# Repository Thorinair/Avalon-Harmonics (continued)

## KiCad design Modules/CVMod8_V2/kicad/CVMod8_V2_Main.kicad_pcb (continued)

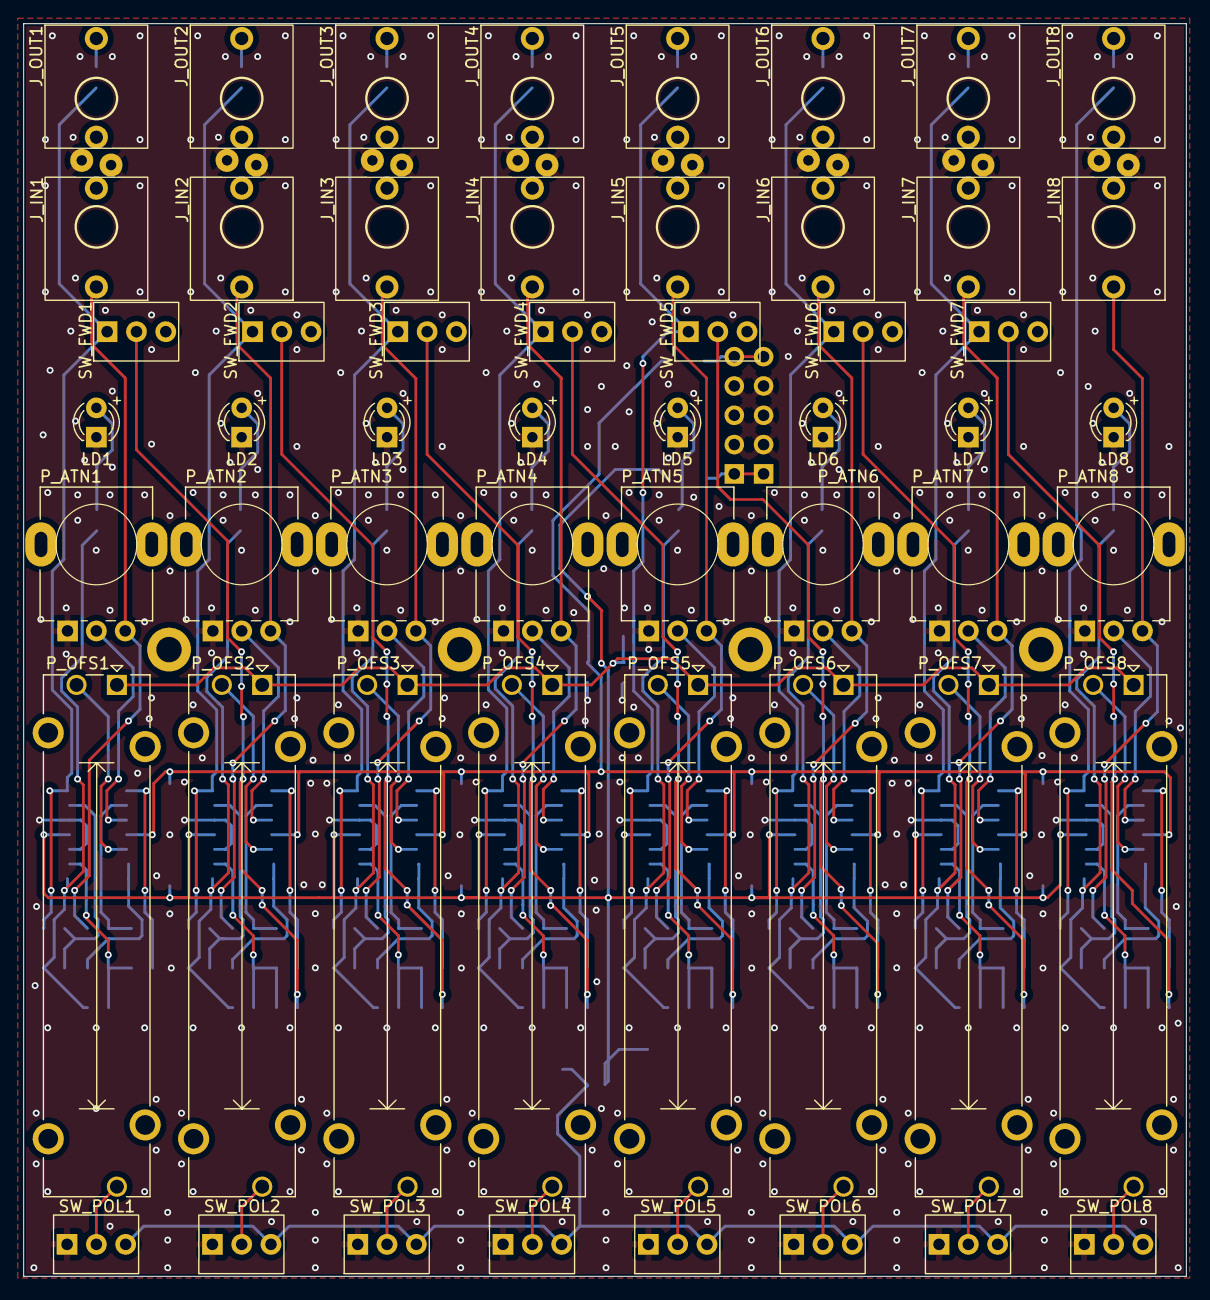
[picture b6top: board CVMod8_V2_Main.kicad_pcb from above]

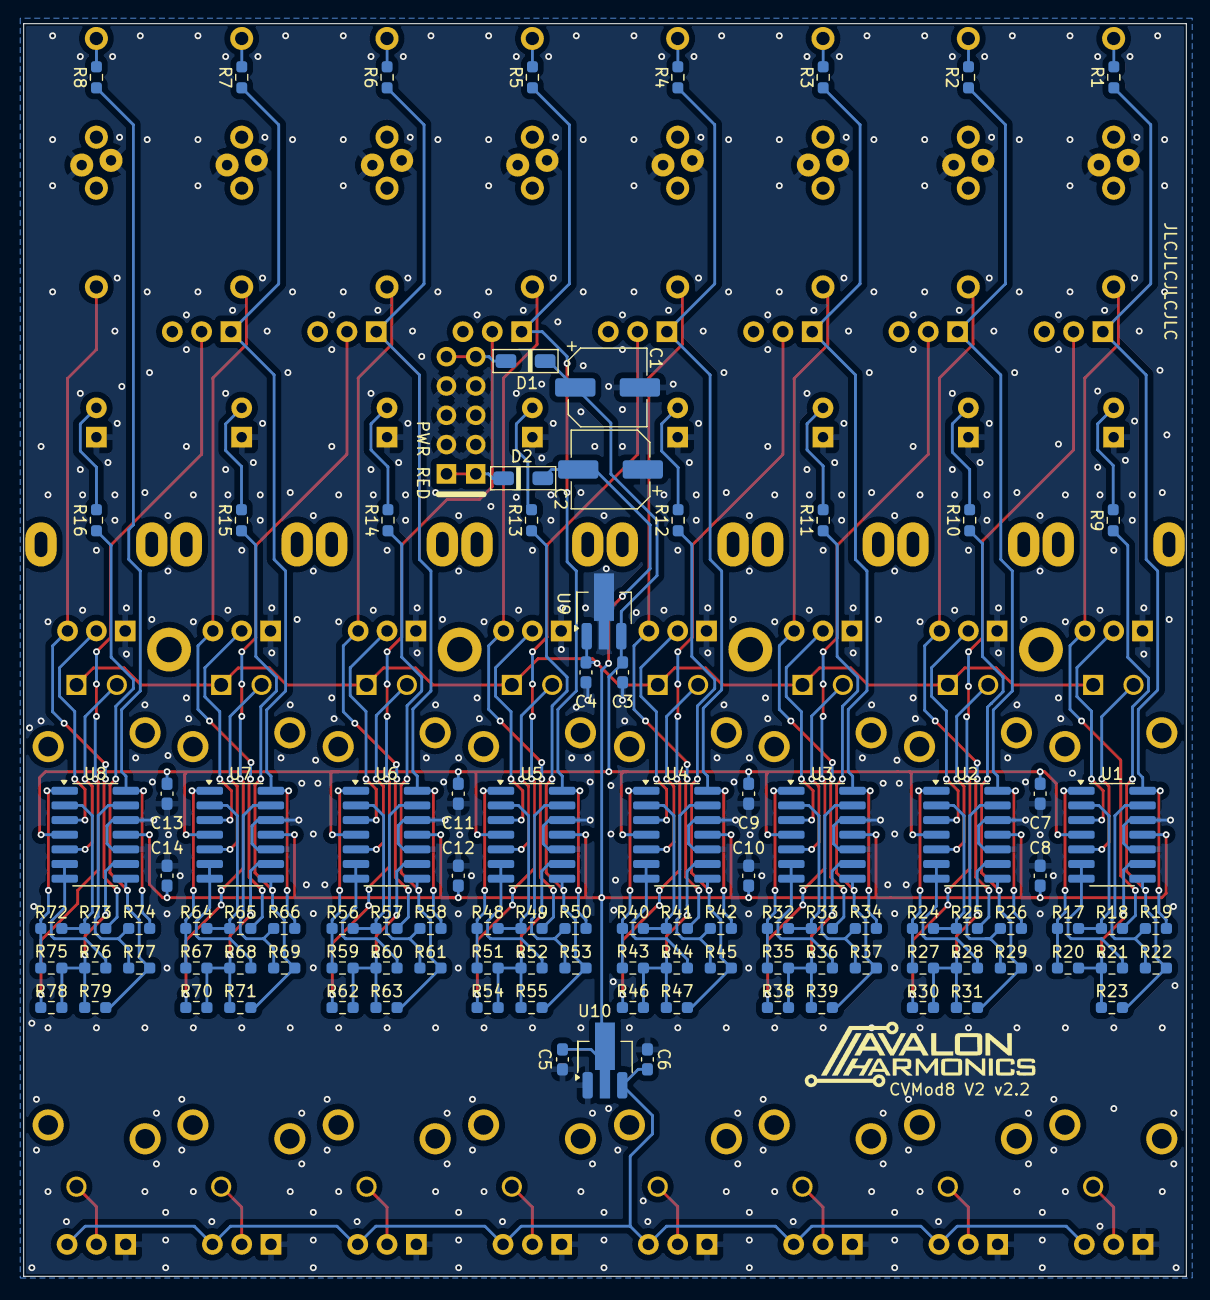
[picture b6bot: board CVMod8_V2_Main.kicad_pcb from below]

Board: 2 copper layers, 100.8 x 108.6 mm, 161 parts (106 on the bottom side), 118 nets.

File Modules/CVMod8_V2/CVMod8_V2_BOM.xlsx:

Avalon Harmonics CVMod8 V2
Qty | Value | Package | Ref | Description | Link |  |  |  | Alt Link
16 | 1k | R-0603 | R1-R16 | Resistor SMD | https://www.tme.eu/de/en/details/smd0603-1k-1%25/smd-resisto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
63 | 100k | R-0603 | R17-R79 | Resistor SMD | https://www.tme.eu/de/en/details/smd0603-100k-1%25/smd-resis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
12 | 0.1uF | C-0603 | C3-C14 | Ceramic Capacitor SMD | https://www.tme.eu/de/en/details/0603b104k500ct/mlcc-smd-cap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
2 | 47uF | E-6.3x5.3mm | C1, C2 | Electrolytic Capacitor SMD | https://www.tme.eu/de/en/details/sc1e476m6l005vr/smd-electro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
2 | FM4001 | SOD123F | D1, D2 | Rectifier Diode SMD | https://www.tme.eu/de/en/details/fm4001-lge/smd-universal-di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
8 | TL074 | SO14 | U1-U8 | Quad Op Amp SMD | https://www.tme.eu/de/en/details/tl074bcdt/smd-operational-a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
1 | 78L05 | SOT89 | U9 | Voltage Regulator 5V SMD | https://www.tme.eu/de/en/details/l78l05abutr/fixed-voltage-r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
1 | 79L05 | SOT89 | U10 | Voltage Regulator -5V NEGATIVE SMD | https://www.tme.eu/de/en/details/lm79l05a-cdi/fixed-voltage-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
8 | B100k | Pot 9mm Tall Trimmer CENTRE DETENT | P_ATN1-P_ATN8 | Potentiometer Plastic | https://www.thonk.co.uk/shop/ttpots/
8 | B100k PTA3043 -2015DPB104 | Bourns Slide Pot 30mm, 15mm L* | P_OFS1-P_OFS8 | Slide Potentiometer | https://www.mouser.de/ProductDetail/Bourns/PTA3043-2015DPB10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
8 | L-937EGW | LED 3mm Dome Bicolor | LD1-LD8 | LED Red/Green | https://www.tme.eu/de/en/details/l-937egw/tht-leds-3mm/kingb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
8 | SPDT ON-ON | Sub-Mini SPDT LOW PROFILE** | SW_POL1-SW_POL8 | Switch | https://www.thonk.co.uk/shop/sub-mini-toggle-switches/
7 | SPDT ON-ON | Sub-Mini SPDT*** | SW_FWD1-SW_FWD7 | Switch | https://www.thonk.co.uk/shop/sub-mini-toggle-switches/
16 | Thonkiconn | PJ398SM | J_IN1-J_IN8, J_OUT1-J_OUT8 | Audio Jack | https://www.thonk.co.uk/shop/thonkiconn/
1 | 2x5 | Male Header 2.54mm**** | PWR | Header Connector | https://www.tme.eu/de/en/details/zl202-80g/pin-headers/connf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
4 | M2*5 | M2 Screw |  | Screw | https://www.aliexpress.com/item/32810872544.html
4 | M2 | M2 Nut |  | Nut | https://www.aliexpress.com/item/1005002177898963.html
4 | M2, 10mm | M2 Standoff***** |  | Standoff | https://www.tme.eu/de/en/details/tfm-m2x10_dr211of/metal-spa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
8 | Black | Pushernut |  | Jack Nut | https://pushermanproductions.com/product/black-smooth-edge-j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
8 | Gold | Pushernut |  | Jack Nut | https://pushermanproductions.com/product/pushernuts-gold-smo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
8 | Black | Thonk Trimmer Topper |  | Trimmer Knob | https://www.thonk.co.uk/shop/tall-trimmer-toppers/
8 | Black | Sifam Sleek Slider Cap****** |  | Slider Knob | https://www.thonk.co.uk/shop/sifam-sleek-slider-caps/
 | Parts with underline are on the front side of the PCB!
 | * Slider pots should be soldered in before mounting the panel. Ensure they are 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
 | ** Use the included extra nut as a washer between the switches and the panel fo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
 | *** For SW_FWD switches, don't use the nut between the panel and the switch. Th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
 | **** Snip off the pins below the switch almost flush to the PCB, otherwise you 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
 | ***** 10mm standoffs are used between the panel and main PCB. Orient them so th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
 | ****** Don't push the caps all the way down, otherwise they will slightly scrap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

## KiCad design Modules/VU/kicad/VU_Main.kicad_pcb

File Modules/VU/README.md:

# Avalon Harmonics VU

**Mono VU meter with envelope follower output**

Now comes as an SMD module. **Features a golden (ENIG coated) panel.** THT version has been discontinued.

VU is a highly compact mono VU meter and envelope follower. The VU display consists of 5 yellow, 3 orange, and 2 red LEDs. The module provides an input jack on the bottom, and a buffered output jack on top, allowing it to be placed right before the master output if so desired. Note that there is no AC coupling, so the module can also be used with slow moving CV signals if so desired.

VU meter can be in either bar or dot mode. This is selected by placing a jumper on the PCB. Leaving the jumper on puts the display in bar mode. The response curve of the VU display depends on the inserted LED driver chip. Three variants of the chip exist and are interchangable on the PCB. The compatible chips are:

* LM3914 - Linear response curve
* LM3915 - Logarithmic response curve, each LED is 3dB
* LM3916 - VU meter response curve, each LED corresponds to following dB levels: +3, +2, +1, 0, -1, -3, -5, -7, -10, -20

In order to drive the the VU display, the signal is first precision rectified, and then passed through an envelope follower. The falloff of this envelope can be adjusted using the HOLD knob, from virtually instantaneous falloff, to a few seconds long one. This envelope follower CV signal is also available on the PEAK output jack, and can be used to control any other module, for instance, to create a sidechain effect. Its voltage ranges from 0V to 9V, depending on the input signal and the set gain (see below).

In order to make the module compatible for different rack setups, a trimmer on the PCB (T_GAIN) allows you to adjust the internal gain of the envelope follower input. This allows you to adjust the VU meter so it hits the peak exactly when it would usually clip on the output module, or whatever is after it, ensuring a more accurate display. This gain does NOT affect the buffered output.

Lastly, the brightness of the last LED can be adjusted with a trimmer on the PCB (T_LED). The brightness can range from around same brightness like all other LEDs, to much brighter. Making the last LED brighter might be desireable to make the peak more visually obvious.

**NOTE: The THT version of this module is rather deep at 66mm to the tip of the power pins, or 70.5mm to the back end of the included cable's connector. Make sure to check if it fits in your case.**

Visit Website: https://avalon-harmonics.com/module/VU/

### Features

* Slim 2 HP design
* Buffered output jack
* Exchangable chips for the response curve
* Adjustable falloff speed
* Envelope follower CV output
* Low power use for the number of LEDs
* Wrong polarity protection
* Size: 2HP
* Depth: 35mm (66mm THT)
* Power: +12V: 31mA, -12V: 14mA (+12V: 36mA, -12V: 15mA THT)

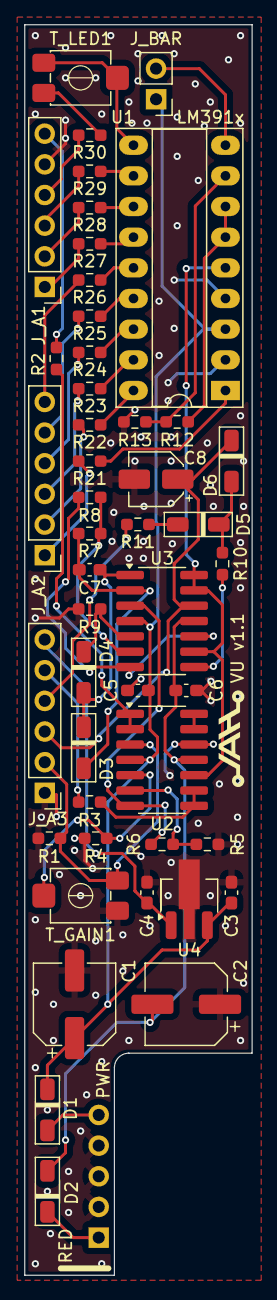
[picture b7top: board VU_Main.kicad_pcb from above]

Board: 2 copper layers, 18.8 x 103.6 mm, 48 parts (0 on the bottom side), 50 nets.

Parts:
C1, C2: 47uF; CP_Elec_6.3x5.3
C3, C4, C5, C6: 0.1uF; C_0603_1608Metric_Pad1.08x0.95mm_HandSolder
C7: 47pF; C_0603_1608Metric_Pad1.08x0.95mm_HandSolder
C8: 10uF; CP_Elec_4x5.4
D1, D2: FM4001; D_SOD-123F_AH
D3, D4, D5, D6: 1N4148W; D_SOD-123F_AH
J_A1, J_A2, J_A3: Conn_01x06_Male; PinHeader_1x06_P2.54mm_Vertical
J_BAR: Conn_01x02_Male; PinHeader_1x02_P2.54mm_Vertical
PWR1: PWR_5_Pin_Angled; Eurorack Power 5 Pin Angled
R1, R4: 100k; R_0603_1608Metric_Pad0.98x0.95mm_HandSolder
R2, R3, R30: 1k; R_0603_1608Metric_Pad0.98x0.95mm_HandSolder
R5, R13: 22k; R_0603_1608Metric_Pad0.98x0.95mm_HandSolder
R6: 330k; R_0603_1608Metric_Pad0.98x0.95mm_HandSolder
R7, R8, R9, R11, R12, R21, R22, R23, R24, R25, R26, R27, R28, R29: 10k; R_0603_1608Metric_Pad0.98x0.95mm_HandSolder
R10: 100; R_0603_1608Metric_Pad0.98x0.95mm_HandSolder
T_GAIN1: B100k; Trimmer_SMD_TOCOS_G43BT
T_LED1: B20k; Trimmer_SMD_TOCOS_G43BT
U1: LM3914N; DIP-18_W7.62mm_Socket_LongPads
U2, U3: TL074; SO-14_3.9x8.65mm_P1.27mm_AH
U4: 78L05; SOT-89-3_Handsoldering

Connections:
+5V: C4.1, J_A3.6, U4.1 (VO)
+12V: C1.1, C3.1, C5.1, D1.1 (K), J_BAR.1, U1.3 (V+), U2.4 (V+), U3.4 (V+), U4.3 (VI)
-12V: C2.2, C6.2, D2.2 (A), U2.11 (V-), U3.11 (V-)
/GAIN: R6.1, U2.7, U3.3 (+)
/HOLD_R: C8.1, D6.1 (K), J_A3.3, U3.12 (+)
/HOLD_S: J_A3.4, R11.2
/IN: J_A3.2, R1.2, T_GAIN1.1, U2.3 (+)
/OUT_PEAK: J_A3.5, R3.1
/OUT_RAW: J_A1.6, R2.1
/PEAK: U1.5 (SIG), U2.10 (+), U3.9 (-), U3.13 (-), U3.14
/RECT: R8.1, U3.7, U3.10 (+)
GND: C1.2, C2.1, C3.2, C4.2, C5.2, C6.1, C8.2, J_A1.5, J_A3.1, PWR1.2 (GND), R1.1, R4.1, R5.2, R9.1, R13.1, T_GAIN1.3, U1.2 (V-), U1.4 (RLO), U2.12 (+), U4.2 (GND)
unnamed: D1.2 (A), PWR1.1 (+12V)
unnamed: D2.1 (K), PWR1.3 (-12V)
unnamed: C7.1, D3.2 (A), R7.2, U3.2 (-)
unnamed: C7.2, D3.1 (K), D4.2 (A), U3.1
unnamed: D4.1 (K), R9.2, U3.5 (+)
unnamed: D5.2 (A), R11.1
unnamed: D5.1 (K), D6.2 (A), R10.1
unnamed: J_A1.1, R27.2
unnamed: J_A1.2, R28.2
unnamed: J_A1.3, R29.2
unnamed: J_A1.4, R30.2
unnamed: J_A2.1, R21.2
unnamed: J_A2.2, R22.2
unnamed: J_A2.3, R23.2
unnamed: J_A2.4, R24.2
unnamed: J_A2.5, R25.2
unnamed: J_A2.6, R26.2
unnamed: J_BAR.2, U1.9 (MODE)
unnamed: R10.2, U3.8
unnamed: R30.1, T_LED1.1
unnamed: R21.1, U1.1 (LED1)
unnamed: R22.1, U1.18 (LED2)
unnamed: R23.1, U1.17 (LED3)
unnamed: R24.1, U1.16 (LED4)
unnamed: R25.1, U1.15 (LED5)
unnamed: R26.1, U1.14 (LED6)
unnamed: R27.1, U1.13 (LED7)
unnamed: R28.1, U1.12 (LED8)
unnamed: R29.1, U1.11 (LED9)
unnamed: T_LED1.2, T_LED1.3, U1.10 (LED10)
unnamed: R12.1, R13.2, U1.8 (REFADJ)
unnamed: R12.2, U1.6 (RHI), U1.7 (REFOUT)
unnamed: R2.2, U2.1, U2.2 (-)
unnamed: R4.2, T_GAIN1.2, U2.5 (+)
unnamed: R5.1, R6.2, U2.6 (-)
unnamed: R3.2, U2.8, U2.9 (-)
unnamed: U2.13 (-), U2.14
unnamed: R7.1, R8.2, U3.6 (-)

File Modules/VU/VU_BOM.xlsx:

Avalon Harmonics VU
Qty | Value | Package | Ref | Description | Link |  |  |  | Alt Link
1 | 100 | R-0603 | R10 | Resistor SMD | https://www.tme.eu/de/en/details/smd0603-100r-1%25/smd-resis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
3 | 1k | R-0603 | R2, R3, R30 | Resistor SMD | https://www.tme.eu/de/en/details/smd0603-1k-1%25/smd-resisto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
14 | 10k | R-0603 | R7-R9, R11, R12, R21-R28, R29* | Resistor SMD | https://www.tme.eu/de/en/details/smd0603-10k-1%25/smd-resist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
2 | 22k | R-0603 | R5, R13 | Resistor SMD | https://www.tme.eu/de/en/details/smd0603-22k-1%25/smd-resist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
2 | 100k | R-0603 | R1, R4 | Resistor SMD | https://www.tme.eu/de/en/details/smd0603-100k-1%25/smd-resis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
1 | 330k | R-0603 | R6 | Resistor SMD | https://www.tme.eu/de/en/details/smd0603-330k-1%25/smd-resis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
1 | B20k | G43BT | T_LED** | Trimmer SMD | https://www.tme.eu/de/en/details/g43bt-b203/single-turn-smd-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
1 | B100k | G43BT | T_GAIN*** | Trimmer SMD | https://www.tme.eu/de/en/details/g43bt-b104/single-turn-smd-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
1 | 47pF | C-0603 | C7 | Ceramic Capacitor SMD | https://www.tme.eu/de/en/details/06035a470kat2a/mlcc-smd-cap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
4 | 0.1uF | C-0603 | C3, C4, C5, C6 | Ceramic Capacitor SMD | https://www.tme.eu/de/en/details/0603b104k500ct/mlcc-smd-cap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
1 | 10uF | E-4x5.4mm | C8 | Electrolytic Capacitor SMD | https://www.tme.eu/de/en/details/vb1e100mb054000ce0/smd-elec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
2 | 47uF | E-6.3x5.3mm | C1, C2 | Electrolytic Capacitor SMD | https://www.tme.eu/de/en/details/sc1e476m6l005vr/smd-electro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
2 | FM4001 | SOD123F | D1, D2 | Rectifier Diode SMD | https://www.tme.eu/de/en/details/fm4001-lge/smd-universal-di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
4 | 1N4148W | SOD123F | D3, D4, D5, D6 | Switching Diode SMD | https://www.tme.eu/de/en/details/1n4148w-dio/smd-universal-d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
1 | IC Socket | DIP-18 Socket | U1 | IC Socket | https://www.tme.eu/de/en/details/icvt-18p/standard-dip-socke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 |  |  |  | https://www.aliexpress.com/item/1005003256812123.html
2 | TL074 | SO14 | U2, U3 | Quad Op Amp SMD | https://www.tme.eu/de/en/details/tl074bcdt/smd-operational-a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
1 | LM391x**** | DIP-18 | U1 | VU LED Driver | https://www.aliexpress.com/item/33015029695.html
1 | 78L05 | SOT89 | U4 | Voltage Regulator 5V SMD | https://www.tme.eu/de/en/details/l78l05abutr/fixed-voltage-r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
5 | OSY5PA3NE4A | LED 3mm Flat | LD1-LD5 | LED Yellow | https://www.tme.eu/de/en/details/osy5pa3ne4a/tht-leds-round/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
3 | OSO5PA3NE4A | LED 3mm Flat | LD6, LD7, LD8 | LED Orange | https://www.tme.eu/de/en/details/oso5pa3ne4a/tht-leds-round/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
2 | OSR5PA3NE4A | LED 3mm Flat | LD9, LD10 | LED Red | https://www.tme.eu/de/en/details/osr5pa3ne4a/tht-leds-round/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
1 | A1M | Pot 9mm Tall Trimmer | P_HOLD | Potentiometer Plastic | https://www.thonk.co.uk/shop/ttpots/
3 | Thonkiconn | PJ398SM | J_IN*****, J_PEAK, J_OUT | Audio Jack | https://www.thonk.co.uk/shop/thonkiconn/
3 | 1x6 | Male Header 2.54mm Angled | J_B1******, J_B2******, J_B3****** | Header Connector | https://www.tme.eu/de/en/details/zl211-40kg-s/pin-headers/co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
1 | 1x2 | Male Header 2.54mm Angled | J_BAR | Header Connector | https://www.tme.eu/de/en/details/zl211-40kg-s/pin-headers/co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
1 | 1x5 | Male Header 2.54mm Angled | PWR | Header Connector | https://www.tme.eu/de/en/details/zl211-40kg-s/pin-headers/co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
1 | Black | Pushernut |  | Jack Nut | https://pushermanproductions.com/product/black-smooth-edge-j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
2 | Gold | Pushernut |  | Jack Nut | https://pushermanproductions.com/product/pushernuts-gold-smo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
1 | Black | Thonk Trimmer Topper |  | Trimmer Knob | https://www.thonk.co.uk/shop/tall-trimmer-toppers/
1 | Black | Jumper 2.54mm |  | Jumper | https://www.aliexpress.com/item/1005001470793144.html
 | Parts with underline are on the front PCB!
 | * Resistors R21-R29 control the brightness of the LEDs. The LEDs chosen in comb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
 | ** Brightness of the last LED can be controlled using the T_LED trimmer.
 | *** Input gain can be adjusted using the T_GAIN trimmer. This does not affect t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
 | **** Use a different IC for different VU response cuirve! LM3915 and LM3916 mig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
 | ***** IMPORTANT: If you have v1.0 Front Board, please solder the 2 joints toget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
 | ****** Solder the plastic side of the angled header on the J_B side, and the me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
Compatible LM391x ICs:
 | LM3914 - Linear response curve
 | LM3915 - Logarithmic response curve, each LED is 3dB
 | LM3916 - VU meter response curve, each LED corresponds to following dB levels: 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

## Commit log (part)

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2022-10-11 Initial commit.
2022-10-11 Align logo.
2022-10-11 Fix image.
2022-10-11 Move image.
2022-10-11 Update image.
2022-10-14 Update license and readme.
2022-12-19 Add printable files.
2022-12-19 Update Nucleus blend.
2022-12-19 Update Nucleus blend again.
2022-12-23 Revamp folders, add blanks, add readmes for all modules.
2022-12-23 Move modules deeper into folder.
2022-12-23 Format module readmes.
2022-12-23 Update readme.
2022-12-26 Add size and depth to readmes.
2023-01-17 Add 2 more blanks, move readme.
2023-01-17 Change capitalization of folder.
2023-01-17 Update Printable readme.
2023-01-18 Update S&S readme.
2023-02-16 Add MiX module.
2023-02-16 Update MiX readme.
2023-02-16 Update MiX readme again.
2023-05-23 Update WF readme.
2023-06-17 Release S&S, R&F, LOGx, WF, MiX
2023-08-15 Fix typo.
2023-08-24 Nucleus release.
2023-09-07 Release CVMod8.
2023-09-23 Update Nucleus BOM with different fuse holders.
2023-10-04 Add SBM-20 as valid tube to BOM.
2023-10-04 Release Alcove, move Blanks around.
2023-12-22 Add links to printed parts on Etsy.
2024-01-10 Add buy link for SubMini switch washers.
2024-02-01 Add RnF slew times.
2024-04-21 Upgrade Nucleus to 1.2, fix triggers not working.
2024-04-21 Update Nucleus printable files.
2024-04-22 Update Nucleus Readme.
2024-04-24 Update Nucleus for fast op amps.
2024-04-26 Update S&S BOM for TL074AC.
2024-05-14 Update LOGx description.
2024-05-26 Add assembled pictures of all modules, adjust some BOMs to not use female headers.
2024-05-27 Release kNOT.
2024-05-28 Release VU.
2024-05-28 Fix a typo in readme.
2024-05-28 Add notice about depth.
2024-05-28 More detailed height.
2024-06-03 Update CVMod8 BOM for new slider pot source.
2024-06-06 Clarify isolated resistor array.
2024-06-06 Update peak LED trimmer in BOM.
2024-06-28 Update S&S for KiCad 8, update capacitor size and BOM.
2024-06-30 Update depth info of 2HP modules.
2024-06-30 Update all BOMs to include a source for single row headers.
2024-07-14 Swap S&S front and back component formatting so it is in line with other modules.
2024-07-15 Update S&S assembled picture.
2024-07-15 Update S&S readme for smaller caps.
2024-08-06 Release iVCA.
2024-08-06 Add website links to all readmes.
2024-08-20 Fix wrong description for 74HC04.
2024-10-15 Add panel graphics and psd files for all modules.
2024-10-17 Remove printed washers as requirement for switches.
2024-11-12 Update all BOMs with a link to a 2x5 power header.
2024-11-15 Release CVMod8 V2.
2024-11-17 Change pot and knob on Nucleus for Thonk one.
2025-02-03 Release Sub-Miniature Switch Wrench.
2025-02-03 Add credit for idea.
2025-02-03 Update URL.
2025-02-04 Update credit wording.
2025-03-05 Release AxB.
2025-04-18 Make resistor networks more obvious.
2025-05-02 Release KickAid.
2025-06-17 Update BOMs with newer links and names.
2025-06-18 Label BOM items better.
2025-06-21 Update BOM for low profile el. capacitors.
2025-09-12 Update some readmes.
2025-10-11 Document a fix for a buzzing issue on KickAid.
2025-10-11 Better description for the fix, and better picture.
2025-10-12 Clarify that it is v1.0 Front Board, not v1.1.
2025-11-05 Update KickAid BOM and Schematic.
2025-11-09 Cleanup all BOMs and update with new URLs.
2025-11-19 Release Pulse.
2025-11-19 Update Pulse readme.
2025-12-16 Update KickAid PCBs.
2025-12-31 Change a resistor on KickAid for better AC coupling.
2026-01-02 Release CVMod4 and X2.
2026-01-13 Add Interactive BOMs, resave all PCBs, move VU to THT.
2026-01-17 Update tab names in all BOMs, fix bi-color LED naming.
2026-01-23 Release PanVCA.
2026-01-31 Release VU SMD version.
2026-02-01 Update label on VU THT schematic.
2026-02-14 Release Pulse specific PulseSensor BOM.
2026-03-23 Release SMD CVMod8 V2.
2026-03-23 Update CVMod8 V2 readme.
2026-05-13 Release MiniDJ.
2026-05-13 Update IBOMs.
2026-05-22 Add credits.
2026-05-24 Update all BOMs with new Pushernut URLs and new power connectors.
2026-05-28 Release CVModH.
2026-06-14 Update X2 to new version.
2026-06-24 Release Puff.
